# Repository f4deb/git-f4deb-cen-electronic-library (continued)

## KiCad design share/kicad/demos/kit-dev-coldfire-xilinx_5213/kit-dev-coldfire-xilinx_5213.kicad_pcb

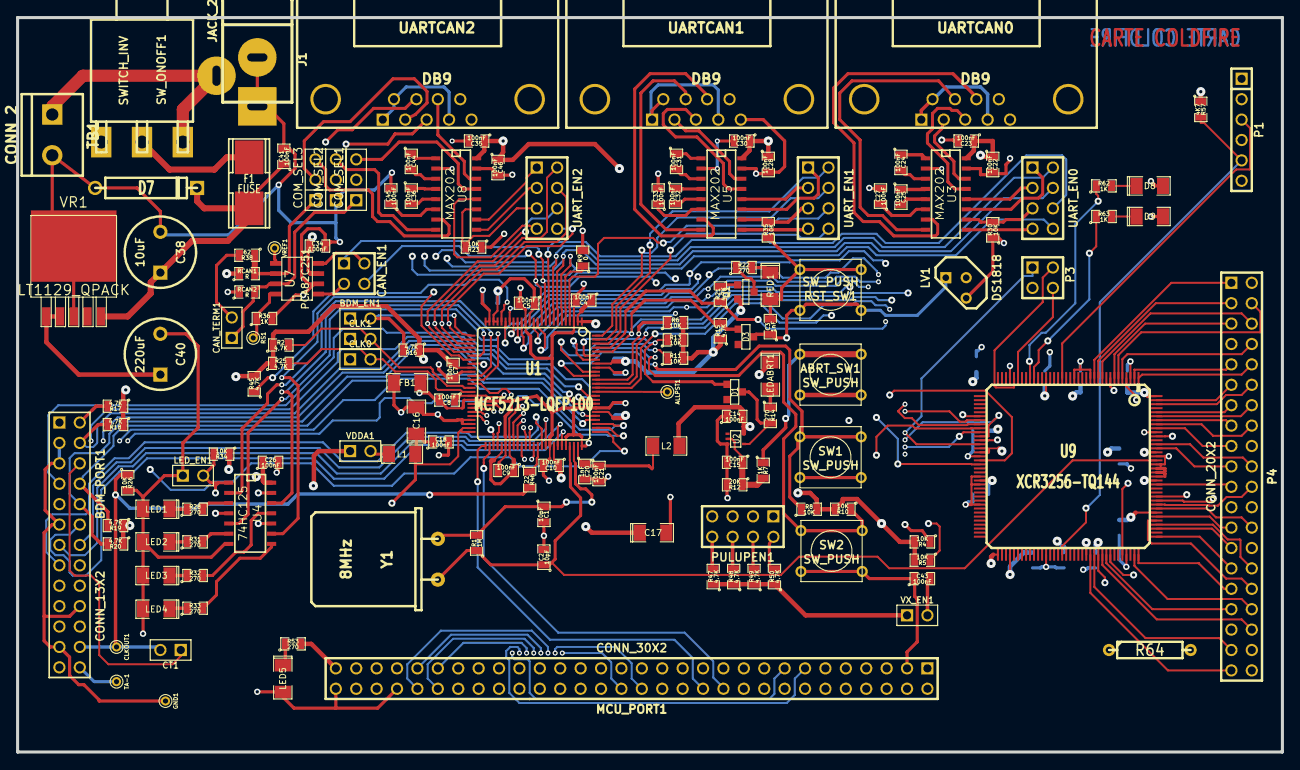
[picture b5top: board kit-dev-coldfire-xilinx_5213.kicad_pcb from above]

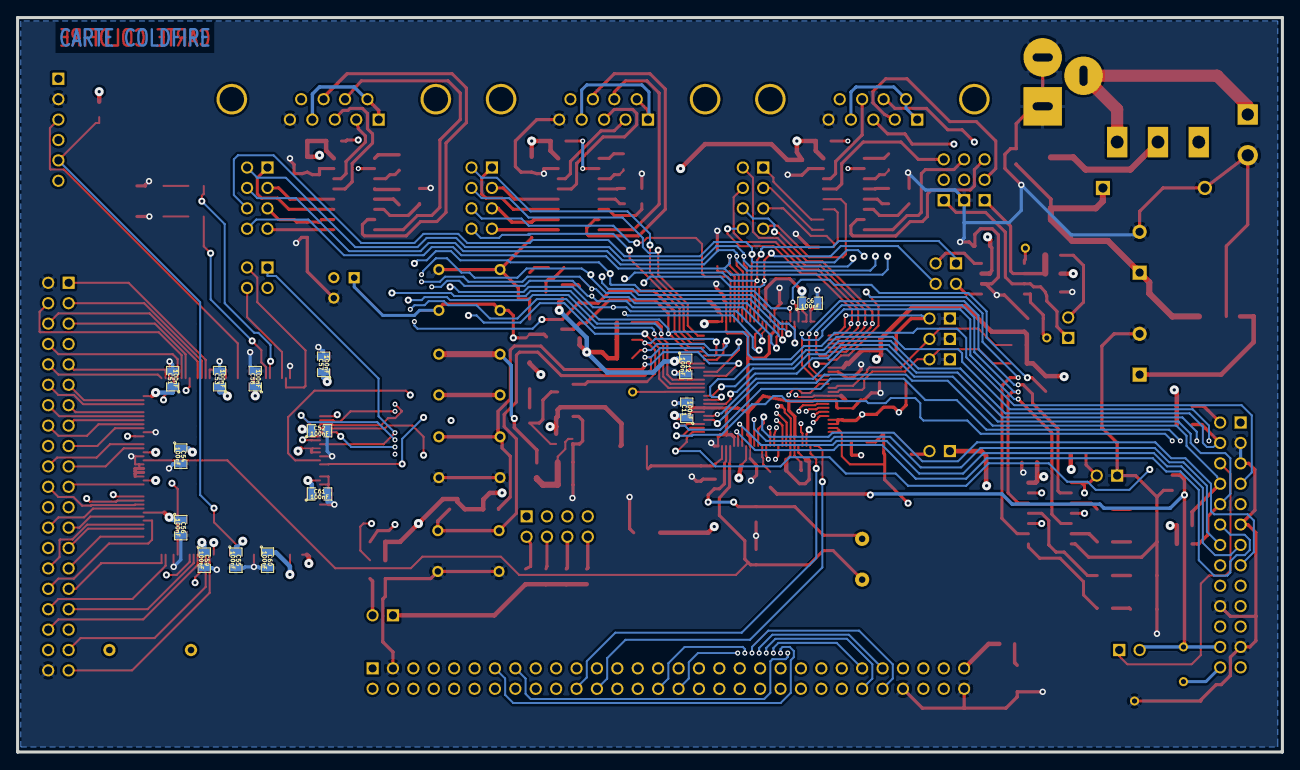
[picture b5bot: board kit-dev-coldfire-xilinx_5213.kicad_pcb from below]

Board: 4 copper layers, 157.5 x 91.4 mm, 162 parts (14 on the bottom side), 209 nets.

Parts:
ABRT_SW1: SW_PUSH; SW_PUSH_SMALL
ALLPST1: CONN_1; PINTST
BDM_EN1: JUMPER; PIN_ARRAY_2X1
BDM_PORT1: CONN_13X2; pin_array_13x2
C1, C2: 10pF; SM0805
C3, C20: 1nF; SM0805
C4, C5, C6, C7, C8, C9, C10, C11, C12, C14, C15, C18, C21, C22, C23, C24, C25, C26, C27, C28, C30, C31, C32, C33, C34, C35, C36, C41, C43, C44, C45, C46, C51, C52, C53, C54, C55, C56, C57, C58, C59, C60, C61: 100nF; SM0805
C16: 10uF; SM1206POL
C17: 100uF; SM1206POL
C38: 10uF; C2V8
C40: 220uF; C2V8
CAN_EN1: CONN_2X2; PIN_ARRAY_2X2
CAN_TERM1: JUMPER; PIN_ARRAY_2X1
CLK0, CLK1: JUMPER; PIN_ARRAY_2X1
CLKOUT1: CONN_1; PINTST
COM_SEL1, COM_SEL2, COM_SEL3: CONN_3; PIN_ARRAY_3X1
CT1: JUMPER; PIN_ARRAY_2X1
D1, D3: BAT54; ST23AK#1
D7: 1N4004; D5
D8, D9: LED; SM1206POL
F1: FUSE; FSUPCMS
FB1: BEAD; SM1206
GND1: CONN_1; PINTST
J1: JACK_2P; JACK_ALIM
L1, L2: 10uH; SM1206
LED1, LED2, LED3, LED4, LED5: LED; SM1206POL
LEDABRT1: RED; SM1206POL
LED_EN1: JUMPER; PIN_ARRAY_2X1
LV1: DS1818; TO92-INVERT
MCU_PORT1: CONN_30X2; PIN_ARRAY_30X2
P1: CONN_6; PIN_ARRAY-6X1
P3: CONN_2X2; PIN_ARRAY_2X2
P4: CONN_20X2; PIN_ARRAY_20X2
PULUPEN1: CONN_4X2; pin_array_4x2
Q1: 3906; SOT23EBC
R1: 1M; SM0805
R2, R15, R16, R17, R18, R19, R20, R21, R25, R45, R47, R48, R49, R50: 4,7K; SM0805
R4, R5, R6, R8, R10, R11, R13, R23, R26, R30, R34, R35: 10K; SM0805
R7, R36, R62, R63: 1K; SM0805
R9: 0; SM0805
R12: 20K; SM0805
R14, R22, R28, R31, R32, R33, R53: 270; SM0805
R38: 62; SM0805
R46: 22; SM0805
R57: 4K7; SM0805
R64: 3,3; R4
RCAN1, RCAN2: R; SM0805
RED1: LED_RESET1; SM1206POL
RS1: CONN_1; PINTST
RST_SW1: SW_PUSH; SW_PUSH_SMALL
SW1, SW2: SW_PUSH; SW_PUSH_SMALL
SW_ONOFF1: SWITCH_INV; SW_SPDT
TA-1: CONN_1; PINTST
TB1: CONN_2; bornier2
U1: MCF5213-LQFP100; VQFP100
U2: 74AHC1G14; SOT353
U3, U5, U8: MAX202; SO16E
U4: 74HC125; SO14E
U7: PCA82C251; SO8E
U9: XCR3256-TQ144; TQFP144
UARTCAN0, UARTCAN1, UARTCAN2: DB9; DB9FC
UART_EN0, UART_EN1, UART_EN2: CONN_4X2; pin_array_4x2
VDDA1: JUMPER; PIN_ARRAY_2X1
VR1: LT1129_QPACK; DPAK5
VREF1: CONN_1; PINTST
VX_EN1: JUMPER; PIN_ARRAY_2X1
Y1: 8MHz; HC-18UH

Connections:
/ALLPST: ALLPST1.1, U1.86
/AN0: MCU_PORT1.10, U1.43
/AN1: MCU_PORT1.12, U1.44
/AN2: MCU_PORT1.14, U1.45
/AN3: MCU_PORT1.16, U1.46
/AN4: MCU_PORT1.18, U1.54
/AN5: MCU_PORT1.20, U1.53
/AN6: MCU_PORT1.22, U1.52
/AN7: MCU_PORT1.24, U1.51
/BKPT-: BDM_PORT1.2, R17.2, U1.76
/CLKIN/EXTAL: C1.1, R1.2, U1.73, Y1.1
/CLKMOD0: CLK0.2, R25.2, U1.40
/CLKMOD1: CLK1.2, R2.2, U1.39
/DDAT0: BDM_PORT1.19, U1.77
/DDAT1: BDM_PORT1.18, U1.78
/DDAT2: BDM_PORT1.17, U1.83
/DDAT3: BDM_PORT1.16, U1.84
/DSCLK: BDM_PORT1.4, R18.2, U1.85
/DSI: BDM_PORT1.8, R19.2, U1.79
/DSO: BDM_PORT1.10, R20.2, U1.80
/DTIN0: MCU_PORT1.34, U1.36, U4.2
/DTIN1: MCU_PORT1.36, U1.37, U4.5
/DTIN2: MCU_PORT1.38, U1.31, U4.12
/DTIN3: MCU_PORT1.40, U1.32, U4.9
/GPT0: MCU_PORT1.49, U1.58
/GPT1: MCU_PORT1.50, U1.59
/GPT2: MCU_PORT1.51, U1.61
/GPT3: MCU_PORT1.52, U1.62
/IRQ-4: MCU_PORT1.33, R8.1, SW1.1, U1.90
/IRQ-5: MCU_PORT1.35, R10.1, SW2.1, U1.91
/IRQ-6: MCU_PORT1.37, R11.1, U1.94
/IRQ-7: D1.1, MCU_PORT1.39, R13.1, U1.95
/JTAG_EN: BDM_EN1.2, R16.2, U1.26
/PST0: BDM_PORT1.15, U1.65
/PST1: BDM_PORT1.14, U1.66
/PST2: BDM_PORT1.13, U1.69
/PST3: BDM_PORT1.12, U1.70
/QSPI_CS0: MCU_PORT1.23, PULUPEN1.3, U1.20
/QSPI_CS3: MCU_PORT1.29, U1.12
/TCLK: BDM_PORT1.24, CLKOUT1.1, CT1.2, R26.1, R46.2
/VDDPLL: C20.1, C21.1, L2.2, U1.74
/inout_user/CANRX: CAN_EN1.4, MCU_PORT1.28, PULUPEN1.7, U1.11
/inout_user/CANTX: CAN_EN1.1, MCU_PORT1.26, PULUPEN1.5, U1.10
/inout_user/CAN_H: CAN_TERM1.1, COM_SEL1.1, RCAN2.2, U7.7
/inout_user/CAN_L: COM_SEL3.1, R38.1, RCAN1.2, U7.6
/inout_user/CTS0: U3.8, UARTCAN0.7
/inout_user/CTS1: U5.8, UARTCAN1.7
/inout_user/CTS2/CANH: COM_SEL1.2, UARTCAN2.7
/inout_user/PWM1: MCU_PORT1.13, U1.38
/inout_user/PWM3: MCU_PORT1.15, U1.33
/inout_user/PWM5: MCU_PORT1.30, U1.60
/inout_user/PWM7: MCU_PORT1.32, U1.63
/inout_user/QSPI_DIN: MCU_PORT1.19, U1.16, U9.46
/inout_user/QSPI_DOUT: MCU_PORT1.17, U1.17, U9.47
/inout_user/QSPI_SCLK: MCU_PORT1.21, PULUPEN1.1, U1.18, U9.48
/inout_user/RCON-: MCU_PORT1.53, R45.1, U1.21
/inout_user/RSTI-: BDM_PORT1.7, D3.1, MCU_PORT1.6, R15.2, U1.96
/inout_user/RTS0: U3.7, UARTCAN0.8
/inout_user/RTS0-: MCU_PORT1.4, R21.1, U1.97
/inout_user/RTS1: U5.7, UARTCAN1.8
/inout_user/RTS2: U8.14, UARTCAN2.8
/inout_user/RXD0: U3.13, UARTCAN0.3
/inout_user/RXD1: U5.13, UARTCAN1.3
/inout_user/RXD2: COM_SEL2.2, UARTCAN2.3
/inout_user/RxD_CAN: CAN_EN1.2, U7.4
/inout_user/TXD0: U3.14, UARTCAN0.2
/inout_user/TXD1: U5.14, UARTCAN1.2
/inout_user/TXD2/CANL: COM_SEL3.2, UARTCAN2.2
/inout_user/TxD_CAN: CAN_EN1.3, U7.1
/inout_user/UCTS0: MCU_PORT1.44, U1.6, UART_EN0.8
/inout_user/UCTS1: MCU_PORT1.11, P3.1, U1.98, U9.49, UART_EN1.8
/inout_user/UCTS2: MCU_PORT1.48, U1.27, UART_EN2.8
/inout_user/URTS0: MCU_PORT1.42, U1.9, UART_EN0.6
/inout_user/URTS1: MCU_PORT1.9, P3.3, U1.4, U9.53, UART_EN1.6
/inout_user/URTS2: MCU_PORT1.46, U1.30, UART_EN2.6
/inout_user/URXD0: MCU_PORT1.43, U1.7, UART_EN0.4
/inout_user/URXD1: MCU_PORT1.7, U1.100, UART_EN1.4
/inout_user/URXD2: MCU_PORT1.47, U1.28, UART_EN2.4
/inout_user/UTXD0: MCU_PORT1.41, U1.8, UART_EN0.2
/inout_user/UTXD1: MCU_PORT1.5, U1.99, UART_EN1.2
/inout_user/UTXD2: MCU_PORT1.45, U1.29, UART_EN2.2
/inout_user/VCCA: C16.1, C18.1, L1.2, MCU_PORT1.55, MCU_PORT1.57, U1.49, U1.50
/xilinx/+3,3V_OUT: P4.38, R64.2
/xilinx/GLCK2: C2.1, R1.1, U1.72, U9.128, Y1.2
/xilinx/IRQ-1: MCU_PORT1.2, R4.1, U1.87, U9.42
/xilinx/IRQ-2: MCU_PORT1.8, R5.1, U1.88, U9.43
/xilinx/IRQ-3: MCU_PORT1.31, R6.1, U1.89, U9.44
/xilinx/LED_TEST1: R62.1, U9.28
/xilinx/LED_TEST2: R63.1, U9.27
/xilinx/QSPI_CS1: MCU_PORT1.25, U1.19, U9.54
/xilinx/QSPI_CS2: MCU_PORT1.27, U1.13, U9.45
/xilinx/TCK: P1.5, R57.2, U9.89
/xilinx/TDI: P1.4, U9.4
/xilinx/TDO: P1.6, U9.104
/xilinx/TMS: P1.3, U9.20
/xilinx/XIL_D0: P4.1, U9.12
/xilinx/XIL_D1: P4.3, U9.11
/xilinx/XIL_D2: P4.5, U9.7
/xilinx/XIL_D3: P4.7, U9.8
/xilinx/XIL_D4: P4.9, U9.2
/xilinx/XIL_D5: P4.11, U9.143
/xilinx/XIL_D6: P4.13, U9.140
/xilinx/XIL_D7: P4.15, U9.138
/xilinx/XIL_D8: P4.17, U9.136
/xilinx/XIL_D9: P4.19, U9.131
/xilinx/XIL_D10: P4.21, U9.122
/xilinx/XIL_D11: P4.23, U9.119
/xilinx/XIL_D12: P4.25, U9.114
/xilinx/XIL_D13: P4.27, U9.111
/xilinx/XIL_D14: P4.29, U9.109
/xilinx/XIL_D15: P4.31, U9.108
/xilinx/XIL_D16: P4.33, U9.100
/xilinx/XIL_D17: P4.35, U9.101
/xilinx/XIL_D18: P4.37, U9.97
/xilinx/XIL_D19: P4.39, U9.96
/xilinx/XIL_D20: P4.4, U9.6
/xilinx/XIL_D21: P4.6, U9.10
/xilinx/XIL_D22: P4.8, U9.5
/xilinx/XIL_D23: P4.10, U9.1
/xilinx/XIL_D24: P4.12, U9.142
/xilinx/XIL_D25: P4.14, U9.139
/xilinx/XIL_D26: P4.16, U9.137
/xilinx/XIL_D27: P4.18, U9.134
/xilinx/XIL_D28: P4.20, U9.132
/xilinx/XIL_D29: P4.22, U9.117
/xilinx/XIL_D30: P4.24, U9.118
/xilinx/XIL_D31: P4.26, U9.116
/xilinx/XIL_D32: P4.28, U9.98
/xilinx/XIL_D33: P4.30, U9.112
/xilinx/XIL_D34: P4.32, U9.113
/xilinx/XIL_D35: P4.34, U9.107
/xilinx/XIL_D36: P4.36, U9.99
GND: BDM_EN1.1, BDM_PORT1.3, BDM_PORT1.5, BDM_PORT1.11, BDM_PORT1.20, BDM_PORT1.23, C1.2, C2.2, C3.2, C4.2, C5.2, C6.2, C7.2, C8.2, C9.2, C10.2, C11.2, C12.2, C14.1, C15.2, C17.2, C20.2, C21.2, C22.2, C26.2, C27.2, C28.2, C33.2, C34.2, C38.2, C40.2, C41.2, C43.1, C45.2, C46.2, C51.2, C52.2, C53.2, C54.2, C55.2, C56.2, C57.2, C58.2, C59.2, C60.2, C61.2, CLK0.1, CLK1.1, COM_SEL2.1, D7.1, D8.2, D9.2, FB1.1, GND1.1, J1.1, J1.2, LED1.2, LED2.2, LED3.2, LED4.2, LED5.2, LED_EN1.1, LV1.3, MCU_PORT1.3, MCU_PORT1.54, MCU_PORT1.60, P1.2, P4.2, P4.40, R9.2, R12.2, R23.1, R26.2, R30.1, R35.1, R36.2, RCAN2.1, RED1.2, RST_SW1.2, SW1.2, SW2.2, TB1.2, U1.3, U1.15, U1.24, U1.25, U1.35, U1.42, U1.56, U1.67, U1.71, U1.75, U1.82, U1.92, U2.3, U3.15, U4.7, U5.15, U7.2, U8.15, U9.3, U9.13, U9.17, U9.33, U9.52, U9.57, U9.59, U9.64, U9.85, U9.105, U9.124, U9.125, U9.126, U9.127, U9.129, U9.135, UARTCAN0.5, UARTCAN1.5, UARTCAN2.5, VR1.3
GNDA: C16.2, C18.2, FB1.2, MCU_PORT1.56, MCU_PORT1.58, U1.47, U1.48
unnamed: ABRT_SW1.1, R7.1
unnamed: BDM_PORT1.6, CT1.1
unnamed: BDM_PORT1.26, TA-1.1
unnamed: C3.1, D3.2, LV1.1, RST_SW1.1
unnamed: C15.1, R7.2, R12.1, U2.2
unnamed: C23.2, U3.2
unnamed: C24.1, U3.1
unnamed: C24.2, U3.3
unnamed: C25.1, U3.4
unnamed: C25.2, U3.5
unnamed: C27.1, U3.6
unnamed: C30.2, U5.2
unnamed: C31.1, U5.1
unnamed: C31.2, U5.3
unnamed: C32.1, U5.4
unnamed: C32.2, U5.5
unnamed: C33.1, U5.6
unnamed: C35.2, U8.2
unnamed: C36.1, U8.4
unnamed: C36.2, U8.5
unnamed: C38.1, C41.1, D7.2, F1.2, VR1.5
unnamed: C43.2, MCU_PORT1.1, VX_EN1.2
unnamed: C44.1, U8.1
unnamed: C44.2, U8.3
unnamed: C45.1, U8.6
unnamed: CAN_TERM1.2, R38.2
unnamed: COM_SEL1.3, U8.13
unnamed: COM_SEL2.3, U8.8
unnamed: COM_SEL3.3, U8.7
unnamed: D1.2, R14.2, U2.4
unnamed: D8.1, R62.2
unnamed: D9.1, R63.2
unnamed: F1.1, SW_ONOFF1.2
unnamed: J1.3, SW_ONOFF1.3, TB1.1
unnamed: L1.1, VDDA1.2
unnamed: LED1.1, R28.1
unnamed: LED2.1, R31.1
unnamed: LED3.1, R32.1
unnamed: LED4.1, R33.1
unnamed: LED5.1, R53.1
unnamed: LEDABRT1.2, R14.1
unnamed: LED_EN1.2, R34.2, U4.1, U4.4, U4.10, U4.13
unnamed: P3.2, U9.32
unnamed: P3.4, U9.31
unnamed: PULUPEN1.2, R50.2
unnamed: PULUPEN1.4, R49.2
unnamed: PULUPEN1.6, R48.2
unnamed: PULUPEN1.8, R47.2
unnamed: Q1.2, R21.2
unnamed: Q1.3, R22.1
unnamed: R9.1, U1.5
unnamed: R22.2, RED1.1
unnamed: R23.2, U8.11, UART_EN2.5
unnamed: R28.2, U4.3
unnamed: R30.2, U3.10, UART_EN0.5
unnamed: R31.2, U4.6
unnamed: R32.2, U4.11
unnamed: R33.2, U4.8
unnamed: R35.2, U5.10, UART_EN1.5
unnamed: R36.1, RS1.1, U7.8
unnamed: R46.1, U1.64
unnamed: U3.9, UART_EN0.7
unnamed: U3.11, UART_EN0.1
unnamed: U3.12, UART_EN0.3
unnamed: U5.9, UART_EN1.7
unnamed: U5.11, UART_EN1.1
unnamed: U5.12, UART_EN1.3
unnamed: U7.5, VREF1.1
unnamed: U8.9, UART_EN2.3
unnamed: U8.10, UART_EN2.1
unnamed: U8.12, UART_EN2.7
unnamed: UARTCAN0.1, UARTCAN0.4, UARTCAN0.6
unnamed: UARTCAN1.1, UARTCAN1.4, UARTCAN1.6
unnamed: UARTCAN2.1, UARTCAN2.4, UARTCAN2.6
VDD: ABRT_SW1.2, BDM_PORT1.9, BDM_PORT1.25, C4.1, C5.1, C6.1, C7.1, C8.1, C9.1, C10.1, C11.1, C12.1, C14.2, C17.1, C22.1, C23.1, C26.1, C28.1, C30.1, C34.1, C35.1, C40.1, C46.1, C51.1, C52.1, C53.1, C54.1, C55.1, C56.1, C57.1, C58.1, C59.1, C60.1, C61.1, L2.1, LEDABRT1.1, LV1.2, MCU_PORT1.59, P1.1, Q1.1, R2.1, R4.2, R5.2, R6.2, R8.2, R10.2, R11.2, R13.2, R15.1, R16.1, R17.1, R18.1, R19.1, R20.1, R25.1, R34.1, R45.2, R47.1, R48.1, R49.1, R50.1, R53.2, R57.1, R64.1, RCAN1.1, U1.1, U1.2, U1.14, U1.22, U1.23, U1.34, U1.41, U1.55, U1.57, U1.68, U1.81, U1.93, U2.5, U3.16, U4.14, U5.16, U7.3, U8.16, U9.24, U9.50, U9.51, U9.58, U9.73, U9.76, U9.95, U9.115, U9.123, U9.130, U9.144, VDDA1.1, VR1.1, VR1.2, VX_EN1.1

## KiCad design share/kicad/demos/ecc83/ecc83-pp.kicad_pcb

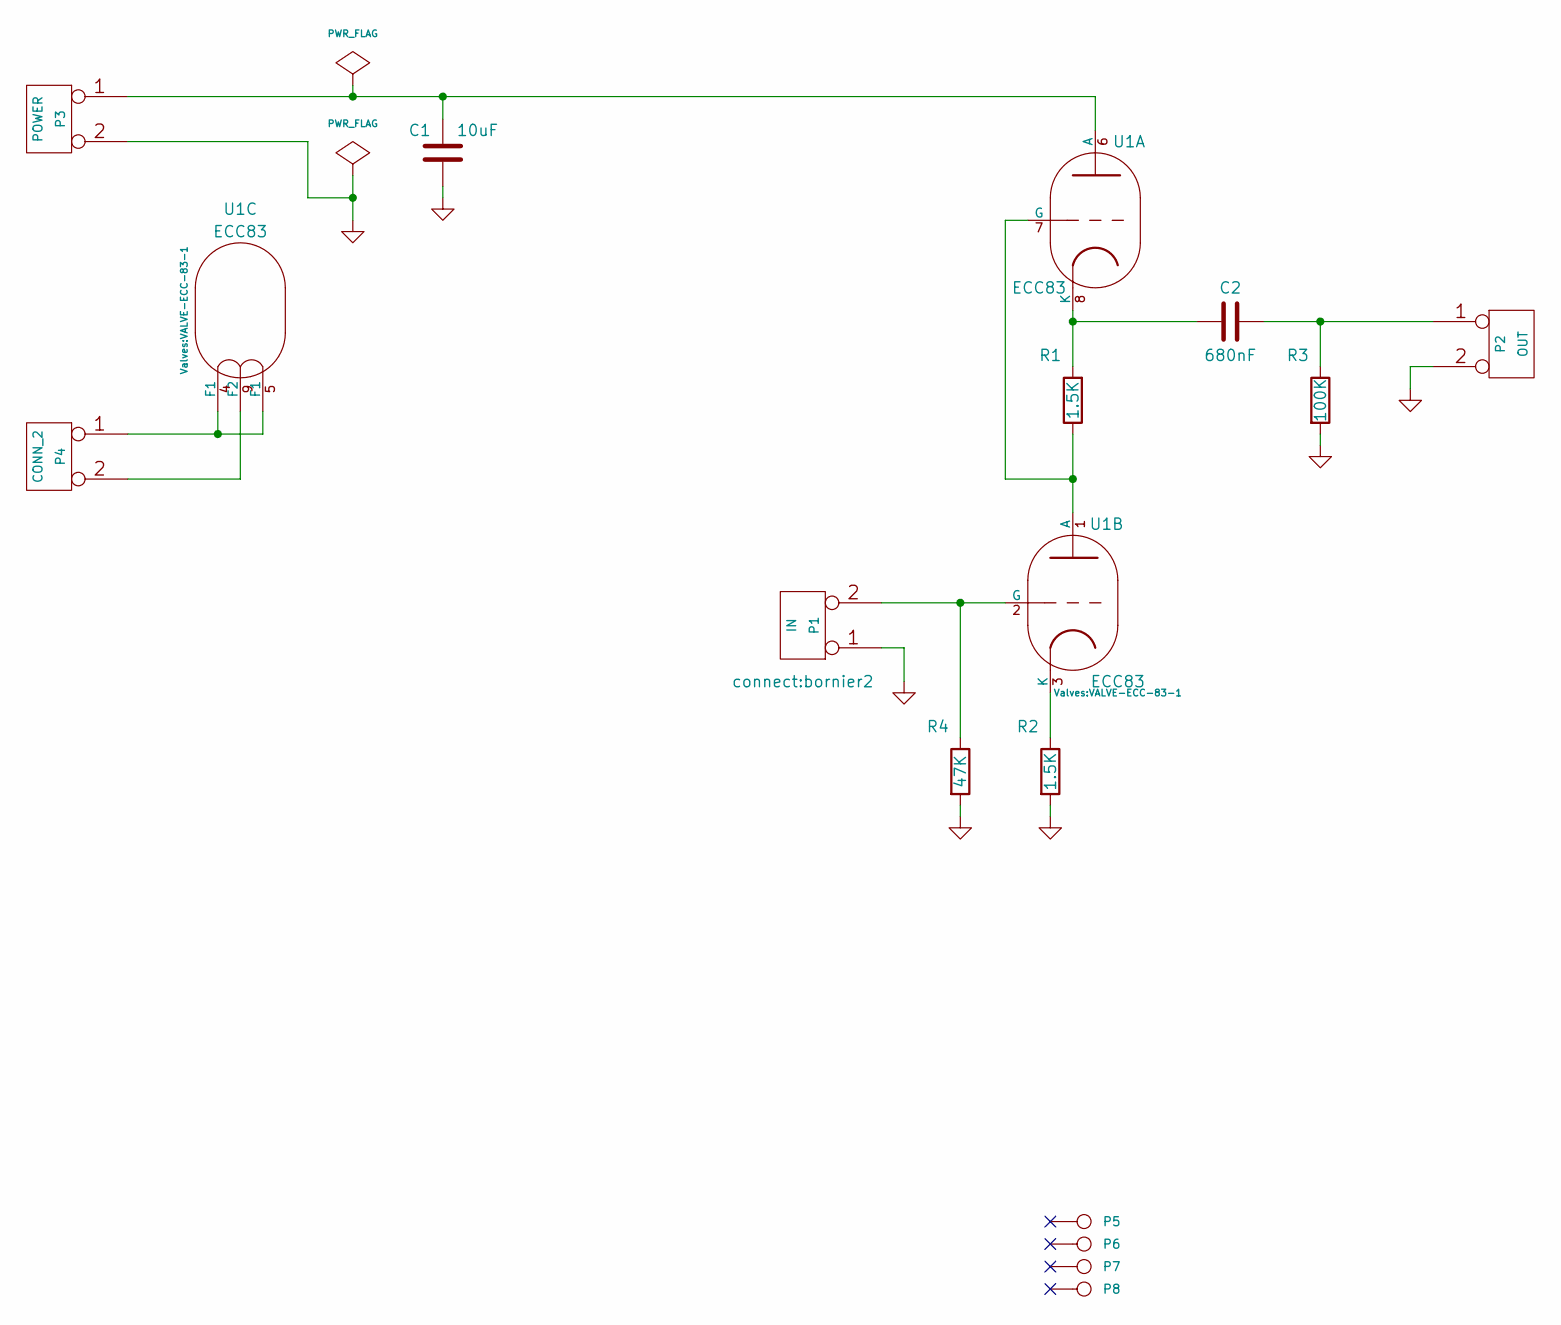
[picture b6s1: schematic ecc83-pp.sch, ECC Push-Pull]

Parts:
C1: 10uF; C2V10
C2: 680nF; C2
P1: IN; bornier2
P2: OUT; bornier2
P3: POWER; bornier2
P4: CONN_2; bornier2
P5, P6, P7, P8: CONN_1; 1pin
R1, R2: 1.5K; R3
R3: 100K; R3
R4: 47K; R3
U1: ECC83; VALVE-ECC-83-1

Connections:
GND: C1.2, P1.1, P2.2 (PM), P3.2 (PM), R2.2, R3.2, R4.2
unnamed: C1.1, P3.1, U1.6 (A)
unnamed: C2.1, P2.1, R3.1
unnamed: C2.2, R1.2, U1.8 (K)
unnamed: P1.2 (PM), R4.1, U1.2 (G)
unnamed: P4.1, U1.4 (F1), U1.5 (F1)
unnamed: P4.2 (PM), U1.9 (F2)
unnamed: R1.1, U1.1 (A), U1.7 (G)
unnamed: R2.1, U1.3 (K)

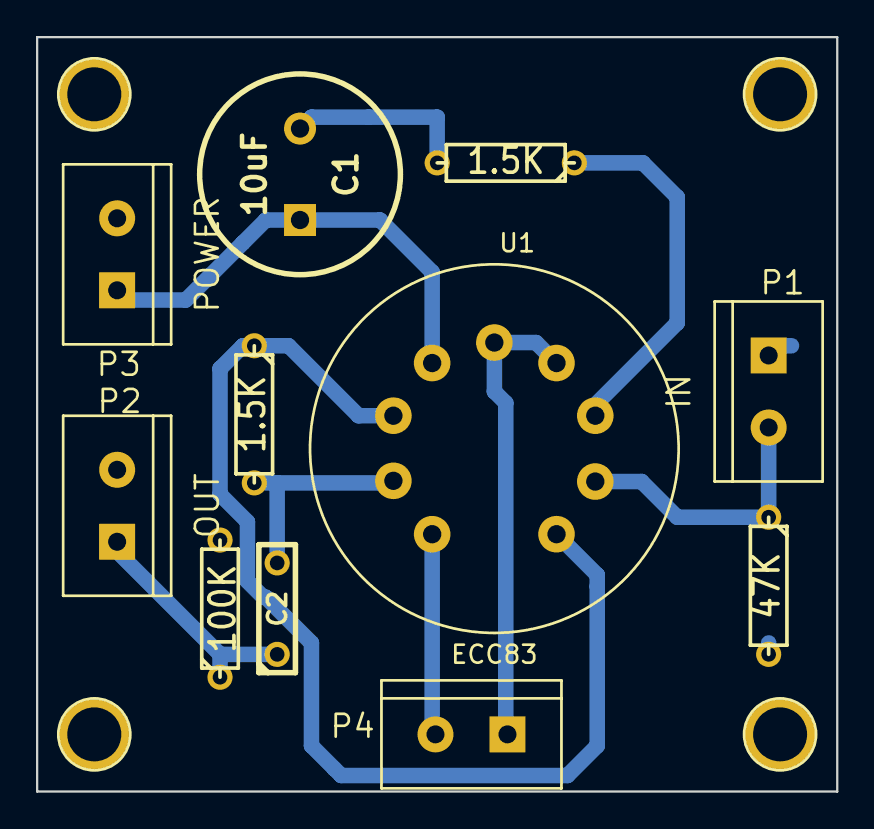
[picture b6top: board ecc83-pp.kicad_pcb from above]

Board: 2 copper layers, 44.5 x 41.9 mm, 15 parts (0 on the bottom side), 9 nets.

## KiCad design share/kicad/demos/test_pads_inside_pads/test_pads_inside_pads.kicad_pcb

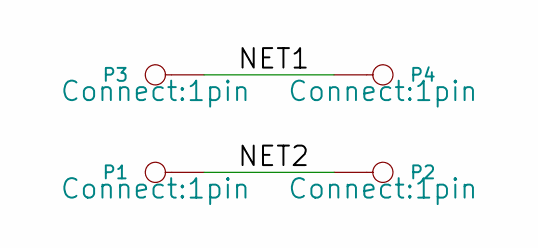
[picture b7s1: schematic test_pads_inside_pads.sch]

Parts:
P1, P2, P3, P4: CONN_1; 1pin

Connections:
/NET1: P3.1, P4.1
/NET2: P1.1, P2.1

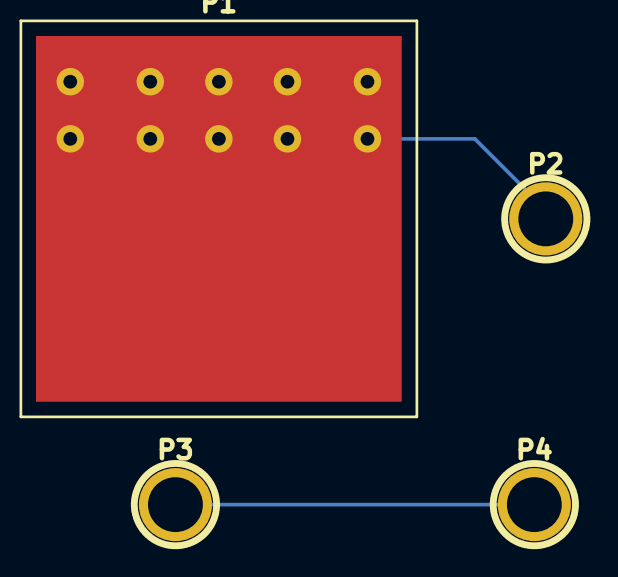
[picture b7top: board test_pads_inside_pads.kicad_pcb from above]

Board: 2 copper layers, 4 parts (0 on the bottom side), 2 nets.

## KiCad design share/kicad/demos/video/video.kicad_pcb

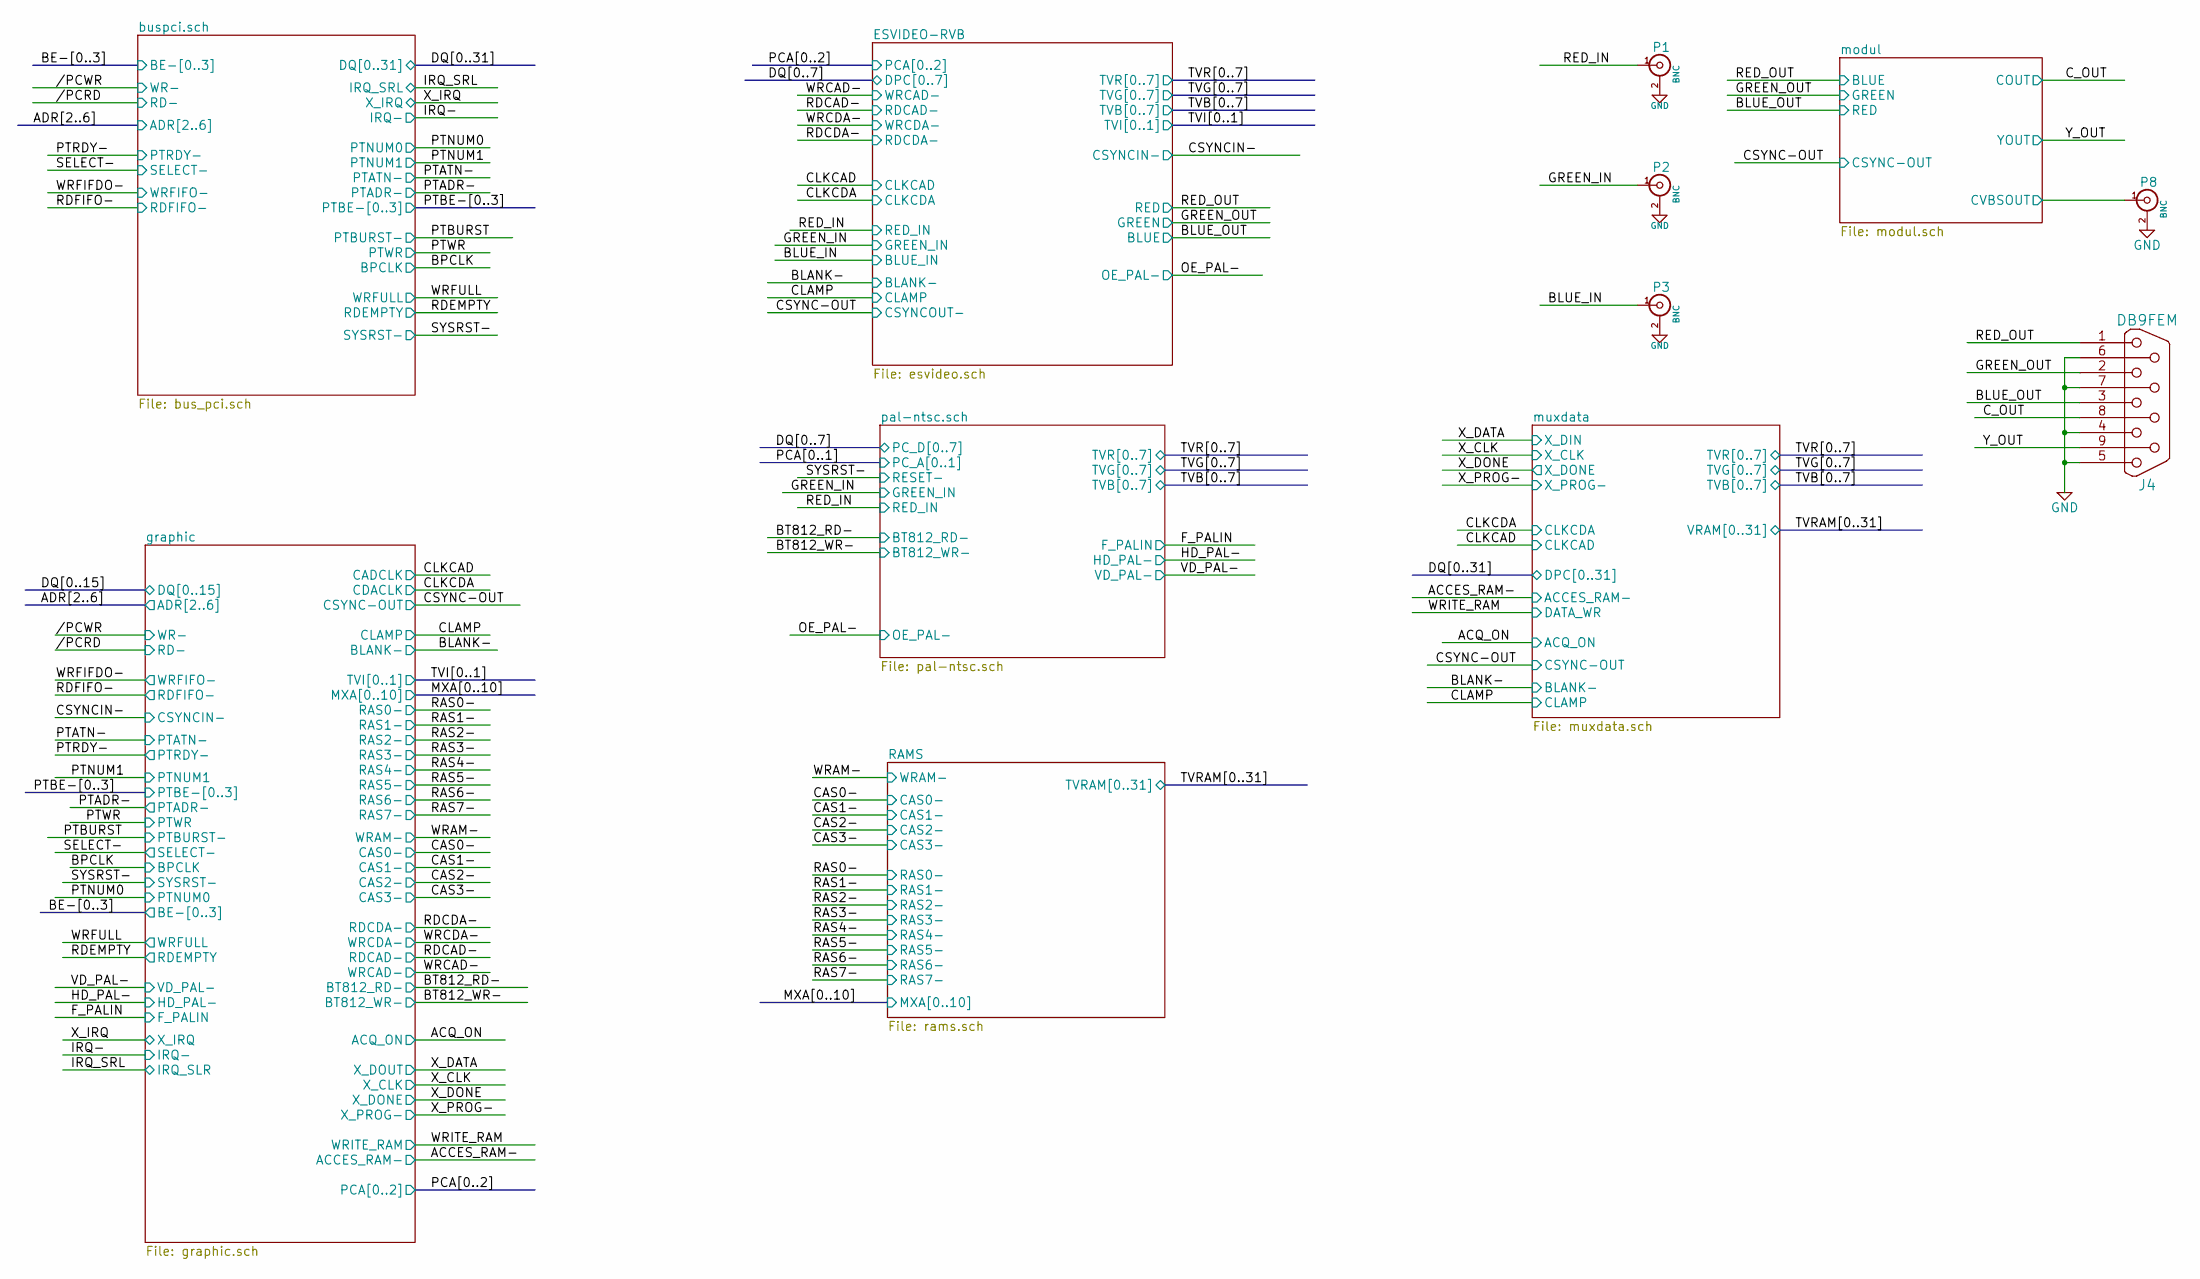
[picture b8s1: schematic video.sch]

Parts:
J4: DB9FEM; DB9FC
P1, P2, P3, P8: BNC; SUBCLICK

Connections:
/ESVIDEO-RVB/BLUE: J4.3; also elsewhere on the board
/ESVIDEO-RVB/BLUE_IN: P3.1 (In); also elsewhere on the board
/ESVIDEO-RVB/GREEN: J4.2; also elsewhere on the board
/ESVIDEO-RVB/GREEN_IN: P2.1 (In); also elsewhere on the board
/ESVIDEO-RVB/RED_IN: P1.1 (In); also elsewhere on the board
/modul/BLEU: J4.1; also elsewhere on the board
/modul/COUT: J4.8; also elsewhere on the board
/modul/CVBSOUT: P8.1 (In); also elsewhere on the board
/modul/YOUT: J4.9; also elsewhere on the board
GND: J4.4, J4.5, J4.6, J4.7, P1.2 (Ext), P2.2 (Ext), P3.2 (Ext), P8.2 (Ext); also elsewhere on the board

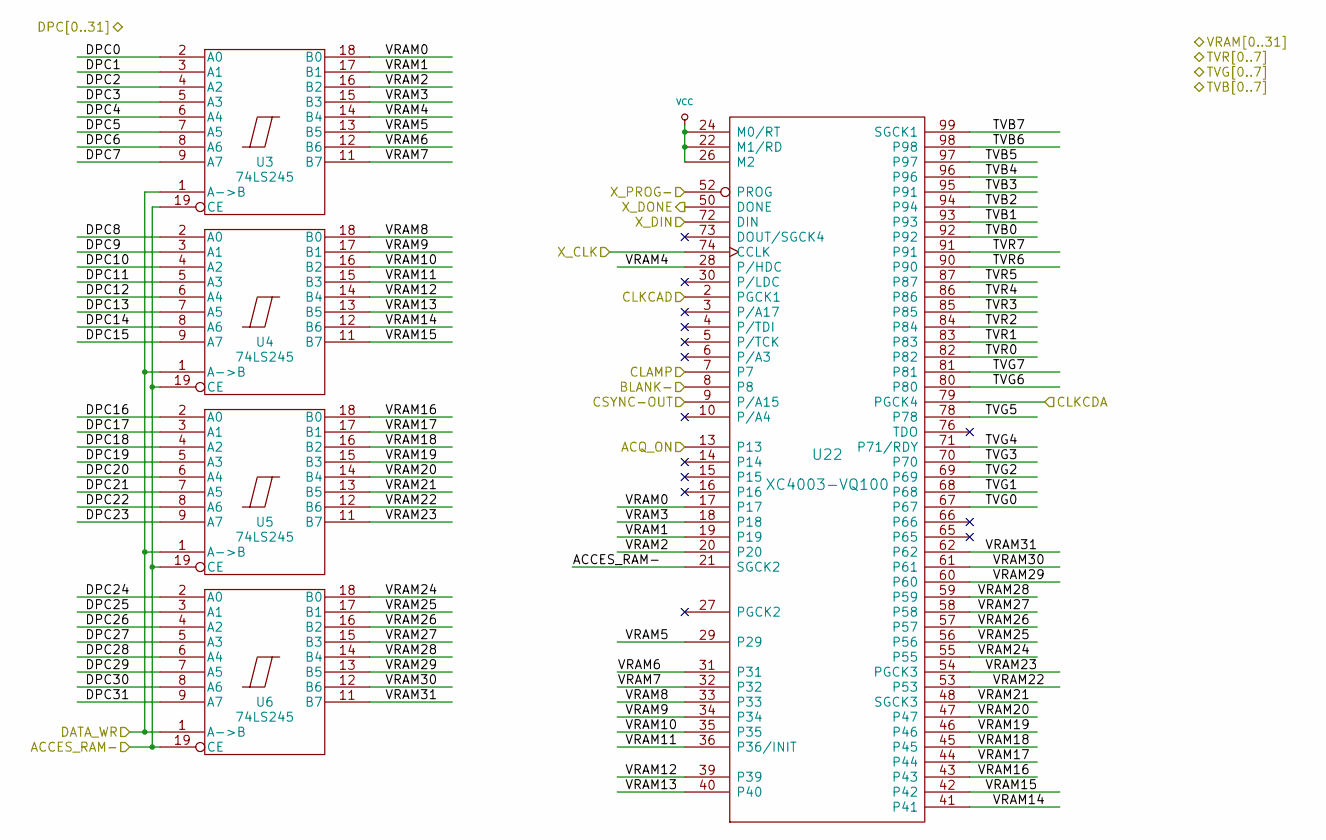
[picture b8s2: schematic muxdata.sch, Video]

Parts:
U3, U4, U5, U6: 74LS245; SO20L
U22: XC4003-VQ100; VQFP100

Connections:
/ESVIDEO-RVB/BLANK-: U22.8; also elsewhere on the board
/ESVIDEO-RVB/CLAMP: U22.7; also elsewhere on the board
/ESVIDEO-RVB/DPC0: U3.2 (A0); also elsewhere on the board
/ESVIDEO-RVB/DPC1: U3.3 (A1); also elsewhere on the board
/ESVIDEO-RVB/DPC2: U3.4 (A2); also elsewhere on the board
/ESVIDEO-RVB/DPC3: U3.5 (A3); also elsewhere on the board
/ESVIDEO-RVB/DPC4: U3.6 (A4); also elsewhere on the board
/ESVIDEO-RVB/DPC5: U3.7 (A5); also elsewhere on the board
/ESVIDEO-RVB/DPC6: U3.8 (A6); also elsewhere on the board
/ESVIDEO-RVB/DPC7: U3.9 (A7); also elsewhere on the board
/ESVIDEO-RVB/TVB0: U22.92; also elsewhere on the board
/ESVIDEO-RVB/TVB1: U22.93; also elsewhere on the board
/ESVIDEO-RVB/TVB2: U22.94; also elsewhere on the board
/ESVIDEO-RVB/TVB3: U22.95 (P91); also elsewhere on the board
/ESVIDEO-RVB/TVB4: U22.96; also elsewhere on the board
/ESVIDEO-RVB/TVB5: U22.97; also elsewhere on the board
/ESVIDEO-RVB/TVB6: U22.98; also elsewhere on the board
/ESVIDEO-RVB/TVB7: U22.99 (SGCK1); also elsewhere on the board
/ESVIDEO-RVB/TVG0: U22.67; also elsewhere on the board
/ESVIDEO-RVB/TVG1: U22.68; also elsewhere on the board
/ESVIDEO-RVB/TVG2: U22.69; also elsewhere on the board
/ESVIDEO-RVB/TVG3: U22.70; also elsewhere on the board
/ESVIDEO-RVB/TVG4: U22.71 (P71/RDY); also elsewhere on the board
/ESVIDEO-RVB/TVG5: U22.78; also elsewhere on the board
/ESVIDEO-RVB/TVG6: U22.80; also elsewhere on the board
/ESVIDEO-RVB/TVG7: U22.81; also elsewhere on the board
/ESVIDEO-RVB/TVR0: U22.82; also elsewhere on the board
/ESVIDEO-RVB/TVR1: U22.83; also elsewhere on the board
/ESVIDEO-RVB/TVR2: U22.84; also elsewhere on the board
/ESVIDEO-RVB/TVR3: U22.85; also elsewhere on the board
/ESVIDEO-RVB/TVR4: U22.86; also elsewhere on the board
/ESVIDEO-RVB/TVR5: U22.87; also elsewhere on the board
/ESVIDEO-RVB/TVR6: U22.90; also elsewhere on the board
/ESVIDEO-RVB/TVR7: U22.91; also elsewhere on the board
/RAMS/TVRAM0: U3.18 (B0), U22.17; also elsewhere on the board
/RAMS/TVRAM1: U3.17 (B1), U22.19; also elsewhere on the board
/RAMS/TVRAM2: U3.16 (B2), U22.20; also elsewhere on the board
/RAMS/TVRAM3: U3.15 (B3), U22.18; also elsewhere on the board
/RAMS/TVRAM4: U3.14 (B4), U22.28 (P/HDC); also elsewhere on the board
/RAMS/TVRAM5: U3.13 (B5), U22.29; also elsewhere on the board
/RAMS/TVRAM6: U3.12 (B6), U22.31; also elsewhere on the board
/RAMS/TVRAM7: U3.11 (B7), U22.32; also elsewhere on the board
/RAMS/TVRAM8: U4.18 (B0), U22.33; also elsewhere on the board
/RAMS/TVRAM9: U4.17 (B1), U22.34; also elsewhere on the board
/RAMS/TVRAM10: U4.16 (B2), U22.35; also elsewhere on the board
/RAMS/TVRAM11: U4.15 (B3), U22.36 (P36/INIT); also elsewhere on the board
/RAMS/TVRAM12: U4.14 (B4), U22.39; also elsewhere on the board
/RAMS/TVRAM13: U4.13 (B5), U22.40; also elsewhere on the board
/RAMS/TVRAM14: U4.12 (B6), U22.41; also elsewhere on the board
/RAMS/TVRAM15: U4.11 (B7), U22.42; also elsewhere on the board
/RAMS/TVRAM16: U5.18 (B0), U22.43; also elsewhere on the board
/RAMS/TVRAM17: U5.17 (B1), U22.44; also elsewhere on the board
/RAMS/TVRAM18: U5.16 (B2), U22.45; also elsewhere on the board
/RAMS/TVRAM19: U5.15 (B3), U22.46; also elsewhere on the board
/RAMS/TVRAM20: U5.14 (B4), U22.47; also elsewhere on the board
/RAMS/TVRAM21: U5.13 (B5), U22.48 (SGCK3); also elsewhere on the board
/RAMS/TVRAM22: U5.12 (B6), U22.53; also elsewhere on the board
/RAMS/TVRAM23: U5.11 (B7), U22.54 (PGCK3); also elsewhere on the board
/RAMS/TVRAM24: U6.18 (B0), U22.55; also elsewhere on the board
/RAMS/TVRAM25: U6.17 (B1), U22.56; also elsewhere on the board
/RAMS/TVRAM26: U6.16 (B2), U22.57; also elsewhere on the board
/RAMS/TVRAM27: U6.15 (B3), U22.58; also elsewhere on the board
/RAMS/TVRAM28: U6.14 (B4), U22.59; also elsewhere on the board
/RAMS/TVRAM29: U6.13 (B5), U22.60; also elsewhere on the board
/RAMS/TVRAM30: U6.12 (B6), U22.61; also elsewhere on the board
/RAMS/TVRAM31: U6.11 (B7), U22.62; also elsewhere on the board
/graphic/ACCES_RAM-: U3.19 (CE), U4.19 (CE), U5.19 (CE), U6.19 (CE), U22.21 (SGCK2); also elsewhere on the board
/graphic/ACQ_ON: U22.13; also elsewhere on the board
/graphic/CADCLK: U22.2 (PGCK1); also elsewhere on the board
/graphic/CDACLK: U22.79 (PGCK4); also elsewhere on the board
/graphic/CSYNC-OUT: U22.9 (P/A15); also elsewhere on the board
/graphic/X_CLK: U22.74 (CCLK); also elsewhere on the board
/graphic/X_DONE: U22.50 (DONE); also elsewhere on the board
/graphic/X_PROG-: U22.52 (PROG); also elsewhere on the board
/muxdata/DATA_WR: U3.1 (A->B), U4.1 (A->B), U5.1 (A->B), U6.1 (A->B); also elsewhere on the board
/muxdata/DPC8: U4.2 (A0); also elsewhere on the board
/muxdata/DPC9: U4.3 (A1); also elsewhere on the board
/muxdata/DPC10: U4.4 (A2); also elsewhere on the board
/muxdata/DPC11: U4.5 (A3); also elsewhere on the board
/muxdata/DPC12: U4.6 (A4); also elsewhere on the board
/muxdata/DPC13: U4.7 (A5); also elsewhere on the board
/muxdata/DPC14: U4.8 (A6); also elsewhere on the board
/muxdata/DPC15: U4.9 (A7); also elsewhere on the board
/muxdata/DPC16: U5.2 (A0); also elsewhere on the board
/muxdata/DPC17: U5.3 (A1); also elsewhere on the board
/muxdata/DPC18: U5.4 (A2); also elsewhere on the board
/muxdata/DPC19: U5.5 (A3); also elsewhere on the board
/muxdata/DPC20: U5.6 (A4); also elsewhere on the board
/muxdata/DPC21: U5.7 (A5); also elsewhere on the board
/muxdata/DPC22: U5.8 (A6); also elsewhere on the board
/muxdata/DPC23: U5.9 (A7); also elsewhere on the board
/muxdata/DPC24: U6.2 (A0); also elsewhere on the board
/muxdata/DPC25: U6.3 (A1); also elsewhere on the board
/muxdata/DPC26: U6.4 (A2); also elsewhere on the board
/muxdata/DPC27: U6.5 (A3); also elsewhere on the board
/muxdata/DPC28: U6.6 (A4); also elsewhere on the board
/muxdata/DPC29: U6.7 (A5); also elsewhere on the board
/muxdata/DPC30: U6.8 (A6); also elsewhere on the board
/muxdata/DPC31: U6.9 (A7); also elsewhere on the board
/muxdata/X_DIN: U22.72 (DIN); also elsewhere on the board
GND: U3.10 (GND), U4.10 (GND), U5.10 (GND), U6.10 (GND), U22.1 (GND), U22.11 (GND), U22.23 (GND), U22.38 (GND), U22.49 (GND), U22.64 (GND), U22.77 (GND), U22.88 (GND); also elsewhere on the board
VCC: U3.20 (VCC), U4.20 (VCC), U5.20 (VCC), U6.20 (VCC), U22.12 (VCC), U22.22 (M1/RD), U22.24 (M0/RT), U22.25 (VCC), U22.26 (M2), U22.37 (VCC), U22.51 (VCC), U22.63 (VCC), U22.75 (VCC), U22.89 (VCC), U22.100 (VCC); also elsewhere on the board
